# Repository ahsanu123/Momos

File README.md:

# 🐍 Introduction

MoMos - Motor Monitoring System, My Final Undergraduate  Project.  
Its Simple  STM32 connected to Raspberry pi  zero 2w, STM32 was used to  sampling motor vibration and current data, then  Raspberry was used for processing and  displaying to localhost.

contain design board of my final project, and program c/c++ and python.

## 💾 Hardware 

Hardware Actually made from 2 separate PCB, first PCB was used to  breaking  out STM32 Module  Pinout (its not backuped), and second PCB was used to place Raspberry Pi zero 2w.

## 🐉 Schematic

## 🌱 Reference

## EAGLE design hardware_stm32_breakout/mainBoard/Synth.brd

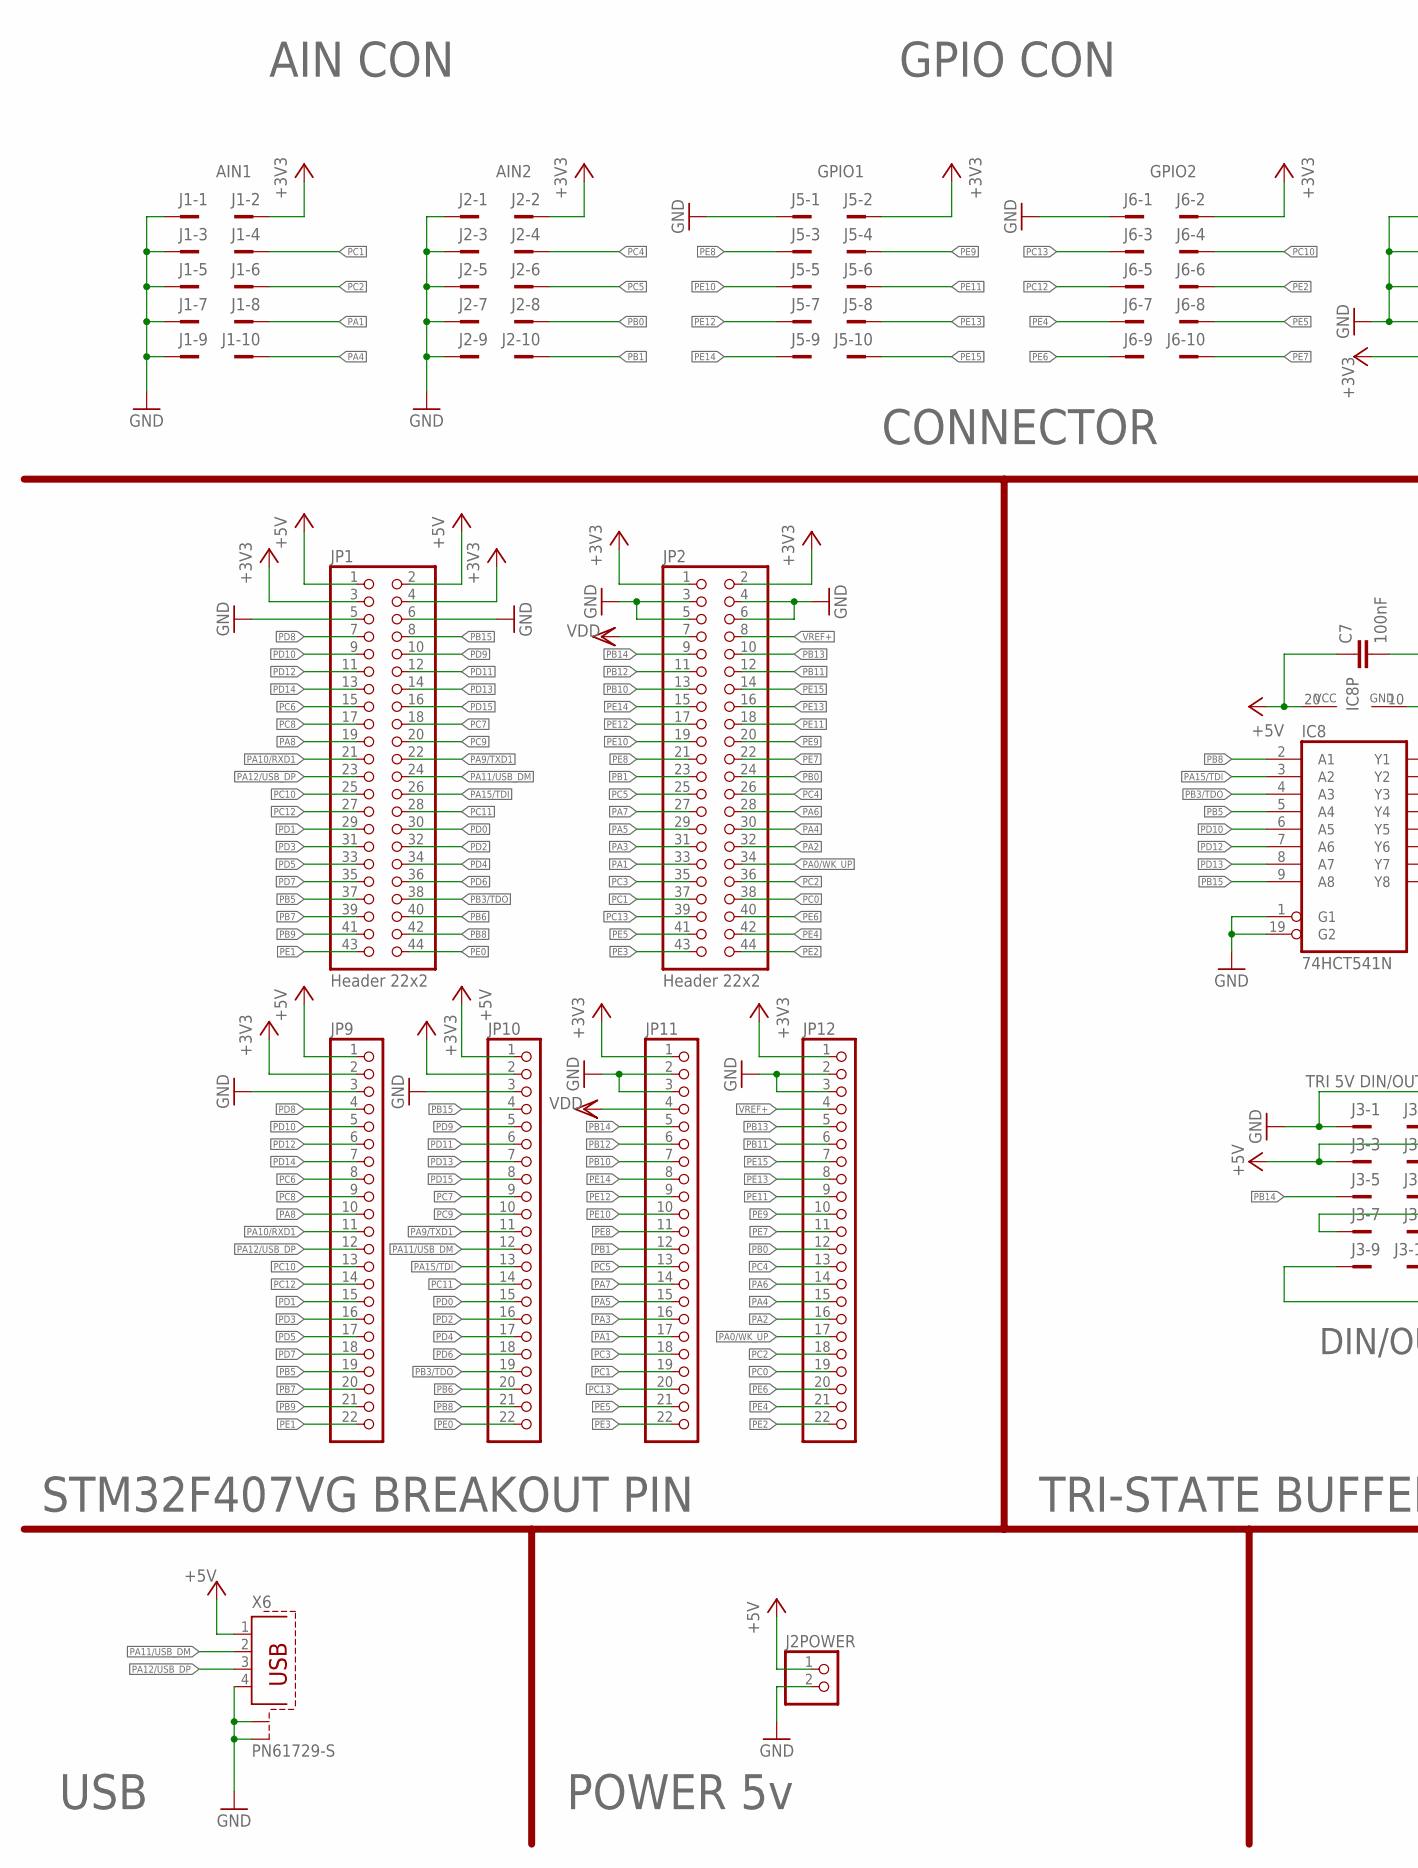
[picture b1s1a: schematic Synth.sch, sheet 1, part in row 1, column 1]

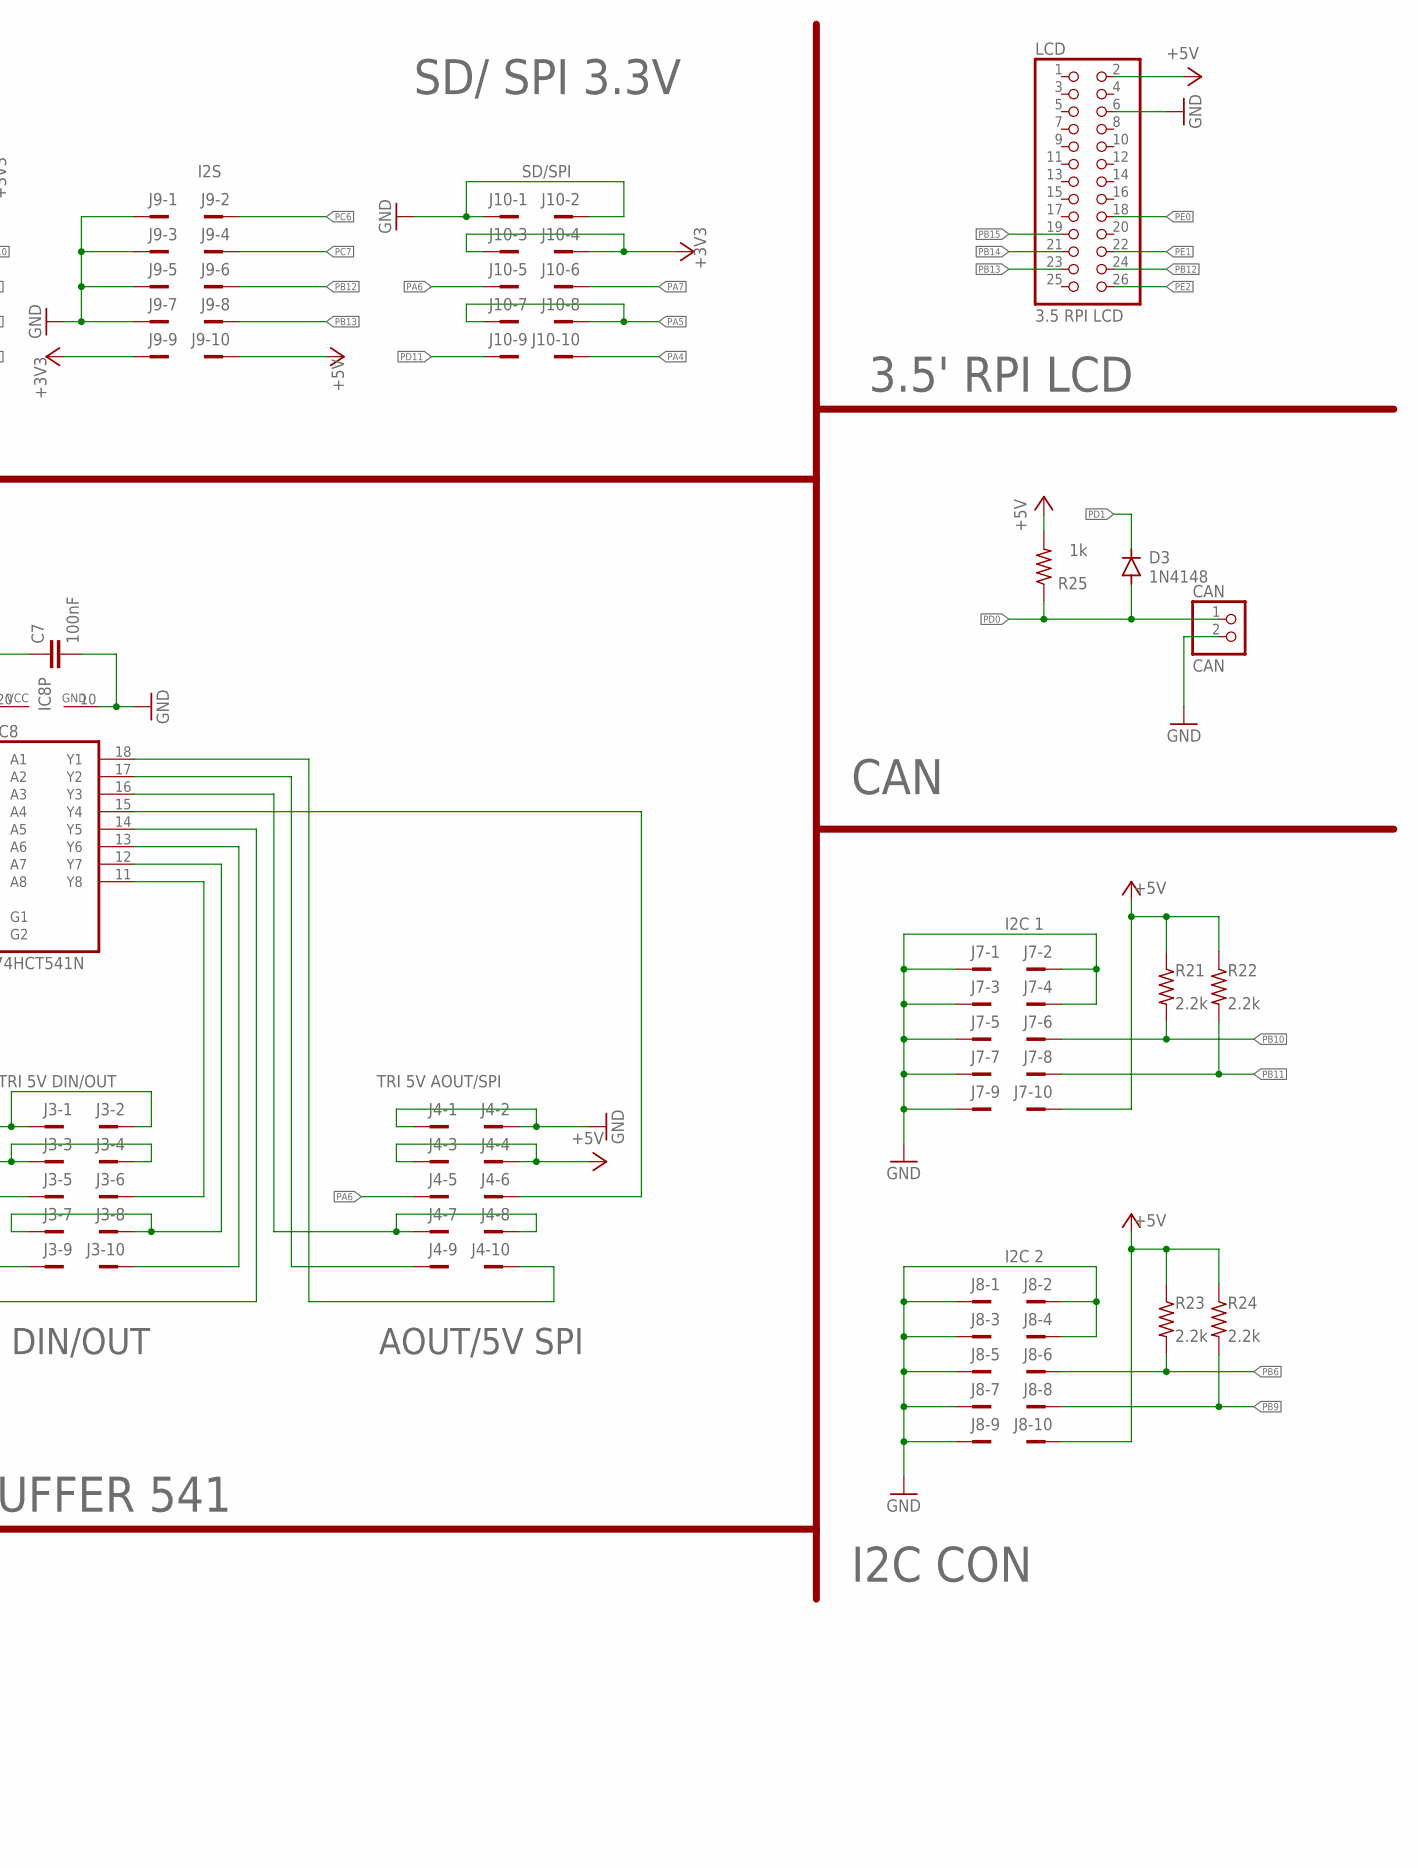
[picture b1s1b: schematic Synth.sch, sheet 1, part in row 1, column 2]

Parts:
C7: 100nF; C025-025X050
CAN: CAN; 1X02
D3: 1N4148; DO35-10
IC8: 74HCT541N; DIL20
J1: AIN1; PAK100/2500-10
J2: AIN2; PAK100/2500-10
J2POWER: PINHD-1X2; 1X02
J3: TRI 5V DIN/OUT; PAK100/2500-10
J4: TRI 5V AOUT/SPI; PAK100/2500-10
J5: GPIO1; PAK100/2500-10
J6: GPIO2; PAK100/2500-10
J7: I2C 1; PAK100/2500-10
J8: I2C 2; PAK100/2500-10
J9: I2S; PAK100/2500-10
J10: SD/SPI; PAK100/2500-10
JP1, JP2: Header 22x2; 2X22
JP9, JP10, JP11, JP12: PINHD-1X22; 1X22
LCD: 3.5 RPI LCD; 2X13
R21, R22, R23, R24: 2.2k; 0207/10
R25: 1k; 0207/10
X6: PN61729-S

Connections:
+3V3: J1.2, J2.2, J5.2, J6.2, J9.9, J10.3, J10.4, JP1.3, JP1.4, JP2.1, JP2.2, JP9.2, JP10.2, JP11.1, JP12.1; also elsewhere on the board
+5V: C7.1, IC8.20 (VCC), J2POWER.1, J3.3, J3.4, J4.3, J4.4, J7.10, J8.10, J9.10, JP1.1, JP1.2, JP9.1, JP10.1, LCD.2, R21.1, R22.1, R23.1, R24.1, R25.2, X6.1; also elsewhere on the board
GND: C7.2, CAN.2, IC8.1 (G1), IC8.10 (GND), IC8.19 (G2), J1.1, J1.3, J1.5, J1.7, J1.9, J2.1, J2.3, J2.5, J2.7, J2.9, J2POWER.2, J3.1, J3.2, J4.1, J4.2, J5.1, J6.1, J7.1, J7.2, J7.3, J7.4, J7.5, J7.7, J7.9, J8.1, J8.2, J8.3, J8.4, J8.5, J8.7, J8.9, J9.1, J9.3, J9.5, J9.7, J10.1, J10.2, JP1.5, JP1.6, JP2.3, JP2.4, JP2.5, JP2.6, JP9.3, JP10.3, JP11.2, JP11.3, JP12.2, JP12.3, LCD.6, X6.4, X6.S1, X6.S2; also elsewhere on the board
unnamed: IC8.15 (Y4), J4.6
unnamed: IC8.12 (Y7), J3.7, J3.8
unnamed: IC8.11 (Y8), J3.6
unnamed: IC8.13 (Y6), J3.10
unnamed: IC8.14 (Y5), J3.9
unnamed: IC8.16 (Y3), J4.7, J4.8
unnamed: IC8.17 (Y2), J4.9
unnamed: IC8.18 (Y1), J4.10
PA0/WK_UP: JP2.34, JP12.17
PA1: J1.8, JP2.33, JP11.17
PA2: JP2.32, JP12.16; also elsewhere on the board
PA3: JP2.31, JP11.16; also elsewhere on the board
PA4: J1.10, J10.10, JP2.30, JP12.15
PA5: J10.7, J10.8, JP2.29, JP11.15
PA6: J4.5, J10.5, JP2.28, JP12.14
PA7: J10.6, JP2.27, JP11.14
PA8: JP1.19, JP9.10; also elsewhere on the board
PA9/TXD1: JP1.22, JP10.11
PA10/RXD1: JP1.21, JP9.11
PA11/USB_DM: JP1.24, JP10.12, X6.2
PA12/USB_DP: JP1.23, JP9.12, X6.3
PA15/TDI: IC8.3 (A2), JP1.26, JP10.13
PB0: J2.8, JP2.24, JP12.12
PB1: J2.10, JP2.23, JP11.12
PB3/TDO: IC8.4 (A3), JP1.38, JP10.19
PB5: IC8.5 (A4), JP1.37, JP9.19
PB6: J8.6, JP1.40, JP10.20, R23.2
PB7: JP1.39, JP9.20
PB8: IC8.2 (A1), JP1.42, JP10.21
PB9: J8.8, JP1.41, JP9.21, R24.2
PB10: J7.6, JP2.13, JP11.7, R21.2
PB11: J7.8, JP2.12, JP12.6, R22.2
PB12: J9.6, JP2.11, JP11.6, LCD.24
PB13: J9.8, JP2.10, JP12.5, LCD.23
PB14: J3.5, JP2.9, JP11.5, LCD.21
PB15: IC8.9 (A8), JP1.8, JP10.4, LCD.19
PC0: JP2.38, JP12.19
PC1: J1.4, JP2.37, JP11.19
PC2: J1.6, JP2.36, JP12.18
PC3: JP2.35, JP11.18
PC4: J2.4, JP2.26, JP12.13
PC5: J2.6, JP2.25, JP11.13
PC6: J9.2, JP1.15, JP9.8
PC7: J9.4, JP1.18, JP10.9
PC8: JP1.17, JP9.9; also elsewhere on the board
PC9: JP1.20, JP10.10
PC10: J6.4, JP1.25, JP9.13
PC11: JP1.28, JP10.14; also elsewhere on the board
PC12: J6.5, JP1.27, JP9.14
PC13: J6.3, JP2.39, JP11.20
PD0: CAN.1, D3.A, JP1.30, JP10.15, R25.1
PD1: D3.C, JP1.29, JP9.15
PD2: JP1.32, JP10.16
PD3: JP1.31, JP9.16; also elsewhere on the board
PD4: JP1.34, JP10.17
PD5: JP1.33, JP9.17
PD6: JP1.36, JP10.18; also elsewhere on the board
PD7: JP1.35, JP9.18
PD8: JP1.7, JP9.4; also elsewhere on the board
PD9: JP1.10, JP10.5; also elsewhere on the board
PD10: IC8.6 (A5), JP1.9, JP9.5
PD11: J10.9, JP1.12, JP10.6
PD12: IC8.7 (A6), JP1.11, JP9.6
PD13: IC8.8 (A7), JP1.14, JP10.7
PD14: JP1.13, JP9.7
PD15: JP1.16, JP10.8
PE0: JP1.44, JP10.22, LCD.18
PE1: JP1.43, JP9.22, LCD.22
PE2: J6.6, JP2.44, JP12.22, LCD.26
PE3: JP2.43, JP11.22
PE4: J6.7, JP2.42, JP12.21
PE5: J6.8, JP2.41, JP11.21
PE6: J6.9, JP2.40, JP12.20
PE7: J6.10, JP2.22, JP12.11
PE8: J5.3, JP2.21, JP11.11
PE9: J5.4, JP2.20, JP12.10
PE10: J5.5, JP2.19, JP11.10
PE11: J5.6, JP2.18, JP12.9
PE12: J5.7, JP2.17, JP11.9
PE13: J5.8, JP2.16, JP12.8
PE14: J5.9, JP2.15, JP11.8
PE15: J5.10, JP2.14, JP12.7
VDD: JP2.7, JP11.4
VREF+: JP2.8, JP12.4

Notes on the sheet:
STM32F407VG BREAKOUT PIN
USB
POWER 5v
AIN CON
GPIO CON
SD/ SPI 3.3V
CONNECTOR
3.5' RPI LCD
CAN
I2C CON
TRI-STATE BUFFER 541
DIN/OUT
AOUT/5V SPI

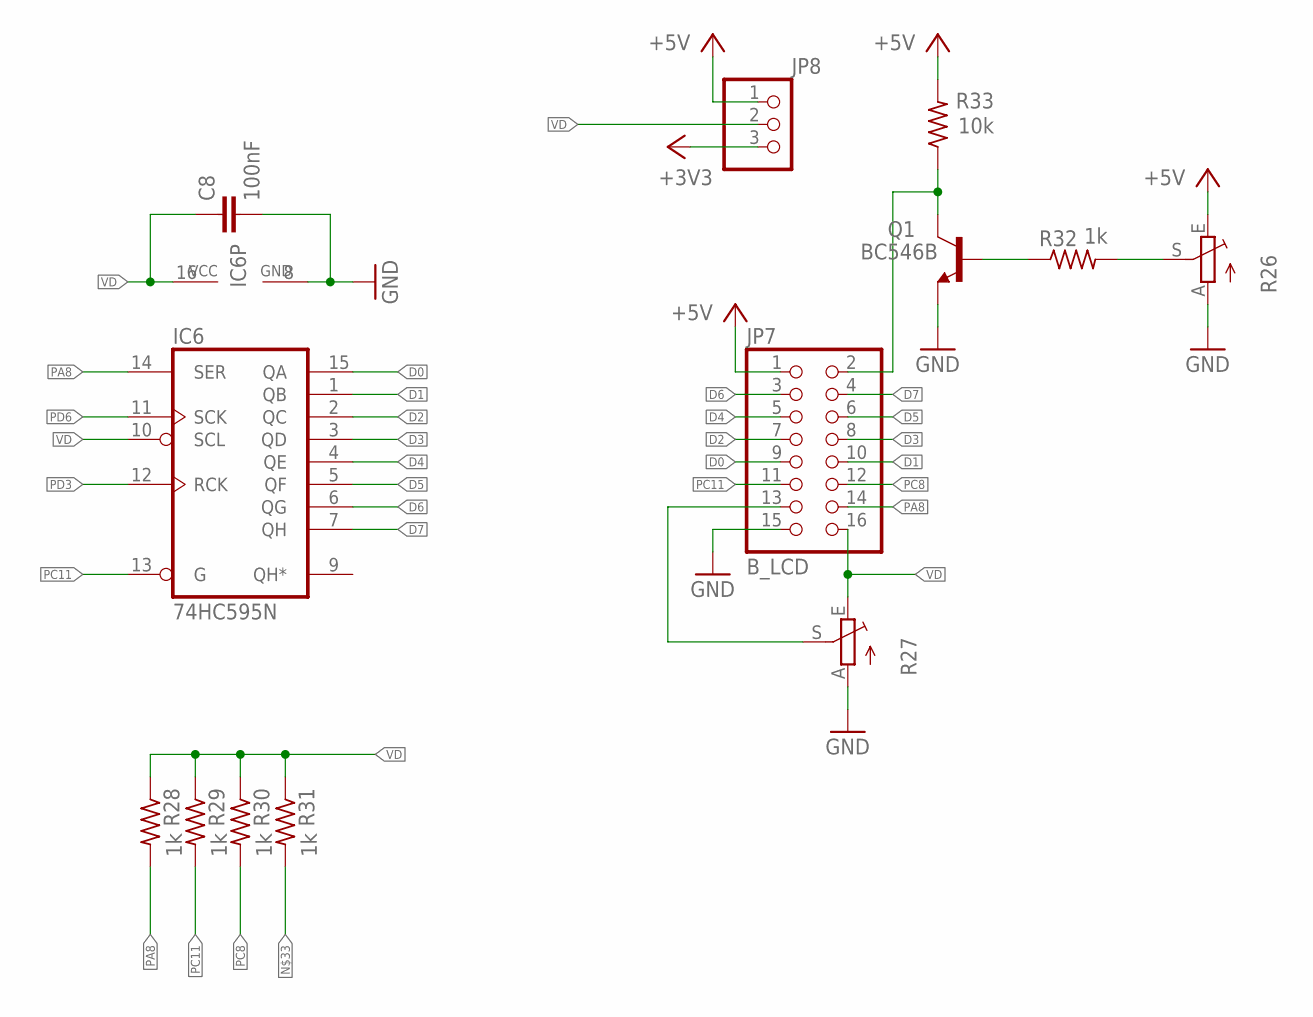
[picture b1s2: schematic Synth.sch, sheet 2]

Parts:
C8: 100nF; C025-025X050
IC6: 74HC595N; DIL16
JP7: B_LCD; 2X08
JP8: PINHD-1X3; 1X03
Q1: BC546B; TO92-EBC
R26, R27: TRIM_EU-CA6V; CA6V
R28, R29, R30, R31, R32: 1k; 0207/10
R33: 10k; 0207/10

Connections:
+3V3: JP8.3; also elsewhere on the board
+5V: JP7.1, JP8.1, R26.E, R33.2; also elsewhere on the board
D0: IC6.15 (QA), JP7.9
D1: IC6.1 (QB), JP7.10
D2: IC6.2 (QC), JP7.7
D3: IC6.3 (QD), JP7.8
D4: IC6.4 (QE), JP7.5
D5: IC6.5 (QF), JP7.6
D6: IC6.6 (QG), JP7.3
D7: IC6.7 (QH), JP7.4
GND: C8.2, IC6.8 (GND), JP7.15, Q1.E, R26.A, R27.A; also elsewhere on the board
unnamed: JP7.13, R27.S
unnamed: JP7.2, Q1.C, R33.1
unnamed: Q1.B, R32.1
unnamed: R26.S, R32.2
PA8: IC6.14 (SER), JP7.14, R28.2; also elsewhere on the board
PC8: JP7.12, R30.2; also elsewhere on the board
PC11: IC6.13 (G), JP7.11, R29.2; also elsewhere on the board
PD3: IC6.12 (RCK); also elsewhere on the board
PD6: IC6.11 (SCK); also elsewhere on the board
VD: C8.1, IC6.10 (SCL), IC6.16 (VCC), JP7.16, JP8.2, R27.E, R28.1, R29.1, R30.1, R31.1

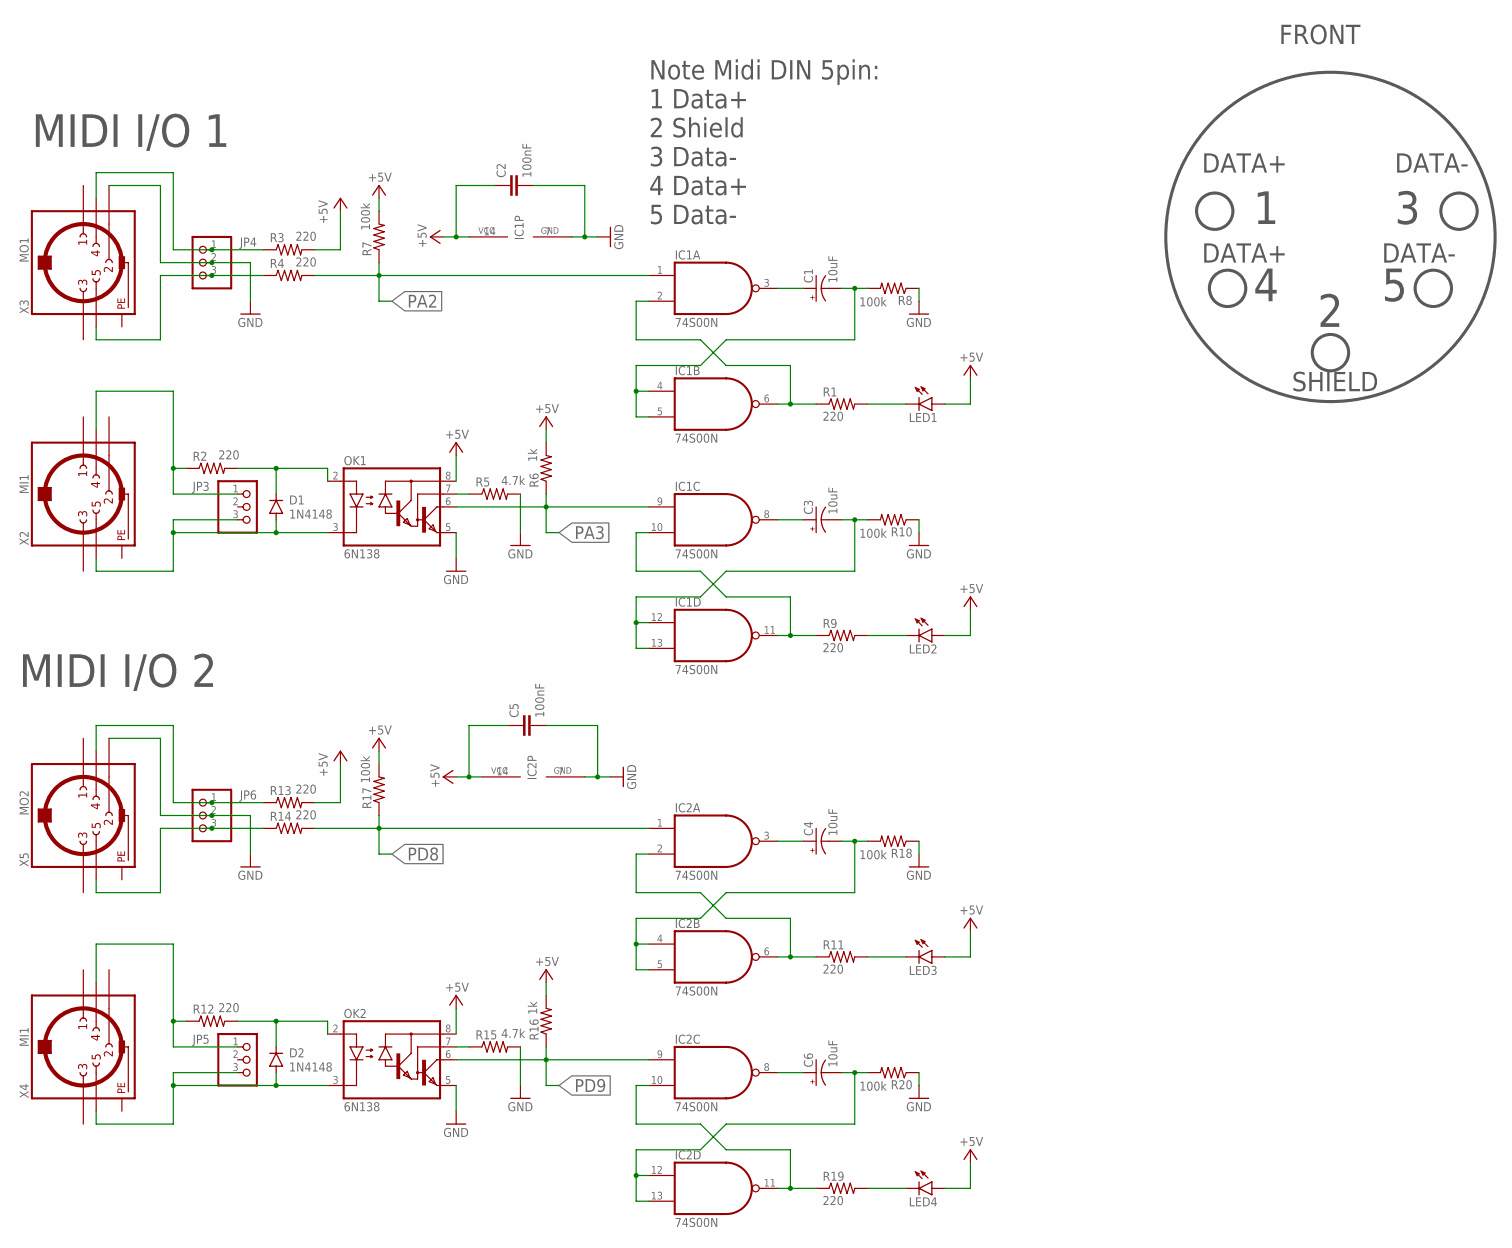
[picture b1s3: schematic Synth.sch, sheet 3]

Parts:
C1, C3, C4, C6: 10uF; E3,5-8
C2, C5: 100nF; C025-025X050
D1, D2: 1N4148; DO35-10
IC1, IC2: 74S00N; DIL14
JP3, JP4, JP5, JP6: PINHD-1X3; 1X03
LED1, LED2, LED3, LED4: LED3MM
OK1, OK2: 6N138; DIL08
R1, R2, R3, R4, R9, R11, R12, R13, R14, R19: 220; 0207/10
R5, R15: 4.7k; 0207/10
R6, R16: 1k; 0207/10
R7, R8, R10, R17, R18, R20: 100k; 0207/10
X2, X4: MI1; MAB5SH
X3: MO1; MAB5SH
X5: MO2; MAB5SH

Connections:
+5V: C2.1, C5.1, IC1.14 (VCC), IC2.14 (VCC), LED1.A, LED2.A, LED3.A, LED4.A, OK1.8 (VCC), OK2.8 (VCC), R3.2, R6.2, R7.2, R13.2, R16.2, R17.2; also elsewhere on the board
GND: C2.2, C5.2, IC1.7 (GND), IC2.7 (GND), JP4.2, JP6.2, OK1.5 (GND), OK2.5 (GND), R5.2, R8.1, R10.1, R15.2, R18.1, R20.1, X3.2, X5.2; also elsewhere on the board
unnamed: D1.C, OK1.2 (A), R2.2
unnamed: D1.A, JP3.3, OK1.3 (C), X2.5
unnamed: JP3.1, R2.1, X2.4
unnamed: D2.C, OK2.2 (A), R12.2
unnamed: OK1.7 (VB), R5.1
unnamed: JP4.3, R4.1, X3.5
unnamed: D2.A, JP5.3, OK2.3 (C), X4.5
unnamed: JP4.1, R3.1, X3.4
unnamed: IC1.2 (I1), IC1.6 (O), R1.1
unnamed: C1.-, IC1.4 (I0), IC1.5 (I1), R8.2
unnamed: C1.+, IC1.3 (O)
unnamed: LED1.K (C), R1.2
unnamed: IC1.10 (I1), IC1.11 (O), R9.1
unnamed: C3.-, IC1.12 (I0), IC1.13 (I1), R10.2
unnamed: C3.+, IC1.8 (O)
unnamed: LED2.K (C), R9.2
unnamed: JP5.1, R12.1, X4.4
unnamed: JP6.3, R14.1, X5.5
unnamed: JP6.1, R13.1, X5.4
unnamed: OK2.7 (VB), R15.1
unnamed: IC2.2 (I1), IC2.6 (O), R11.1
unnamed: C4.-, IC2.4 (I0), IC2.5 (I1), R18.2
unnamed: C4.+, IC2.3 (O)
unnamed: LED3.K (C), R11.2
unnamed: IC2.10 (I1), IC2.11 (O), R19.1
unnamed: C6.-, IC2.12 (I0), IC2.13 (I1), R20.2
unnamed: C6.+, IC2.8 (O)
unnamed: LED4.K (C), R19.2
PA2: IC1.1 (I0), R4.2, R7.1; also elsewhere on the board
PA3: IC1.9 (I0), OK1.6 (VO), R6.1; also elsewhere on the board
PD8: IC2.1 (I0), R14.2, R17.1; also elsewhere on the board
PD9: IC2.9 (I0), OK2.6 (VO), R16.1; also elsewhere on the board
PE: X2.PE, X2.PE@ (PE), X3.PE, X3.PE@ (PE), X4.PE, X4.PE@ (PE), X5.PE, X5.PE@ (PE)

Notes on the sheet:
Note Midi DIN 5pin: 1 Data+ 2 Shield 3 Data- 4 Data+ 5 Data-
MIDI I/O 1
MIDI I/O 2
FRONT
DATA+
DATA-
SHIELD

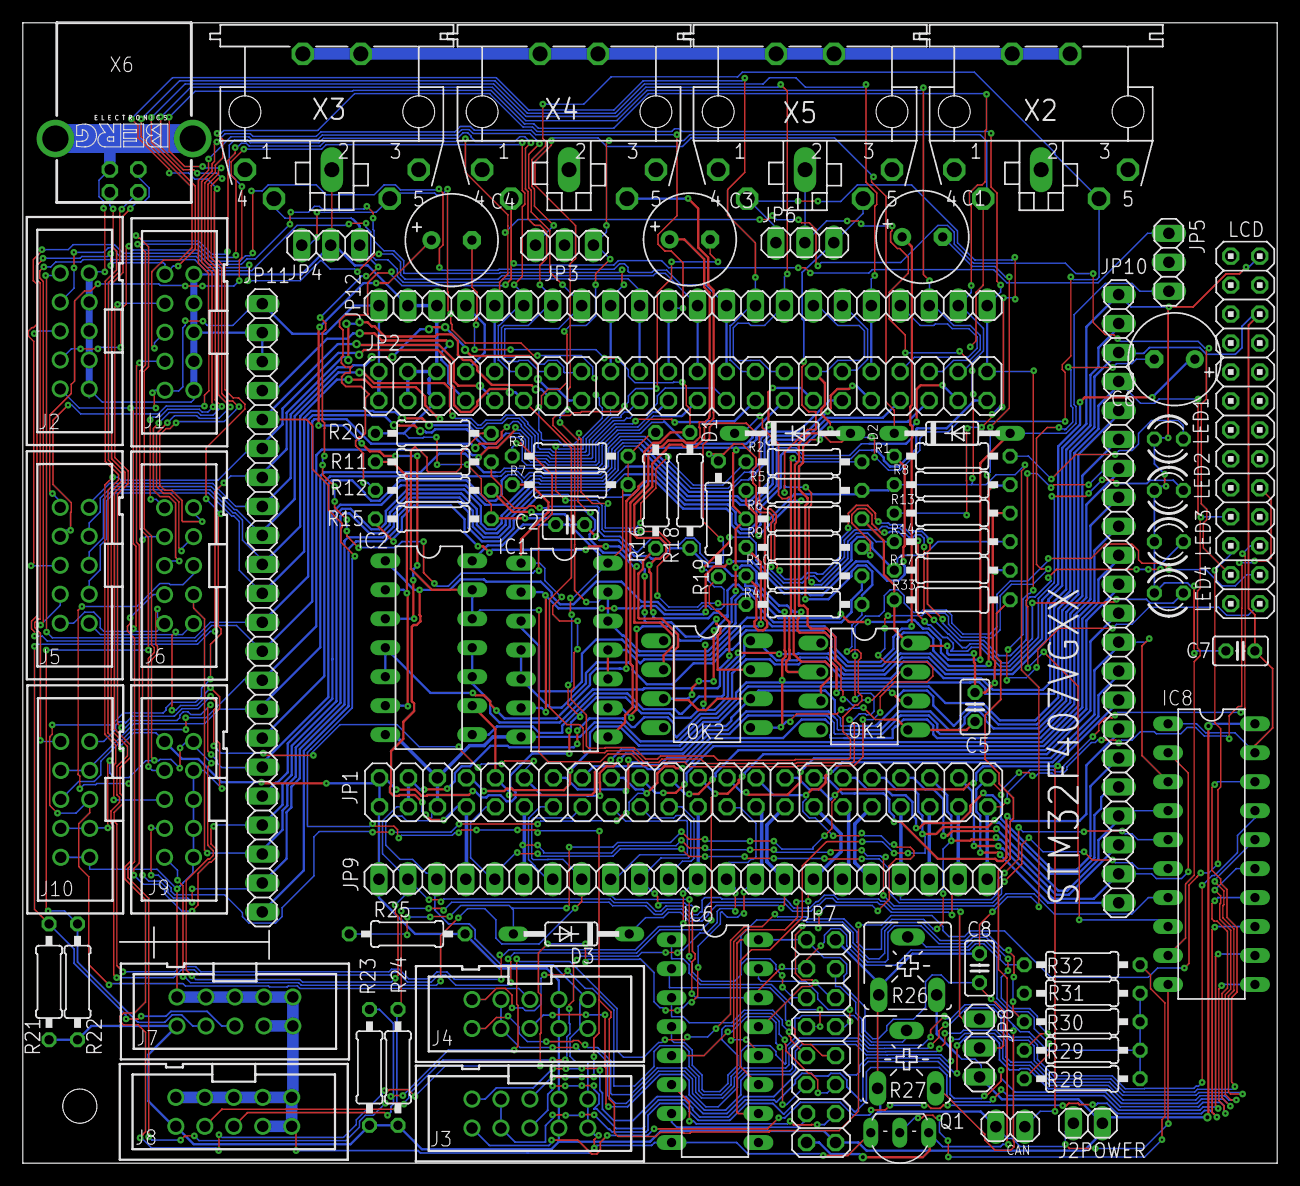
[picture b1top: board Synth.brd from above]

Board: 2 copper layers, 110.0 x 100.0 mm, 85 parts (0 on the bottom side), 129 nets.

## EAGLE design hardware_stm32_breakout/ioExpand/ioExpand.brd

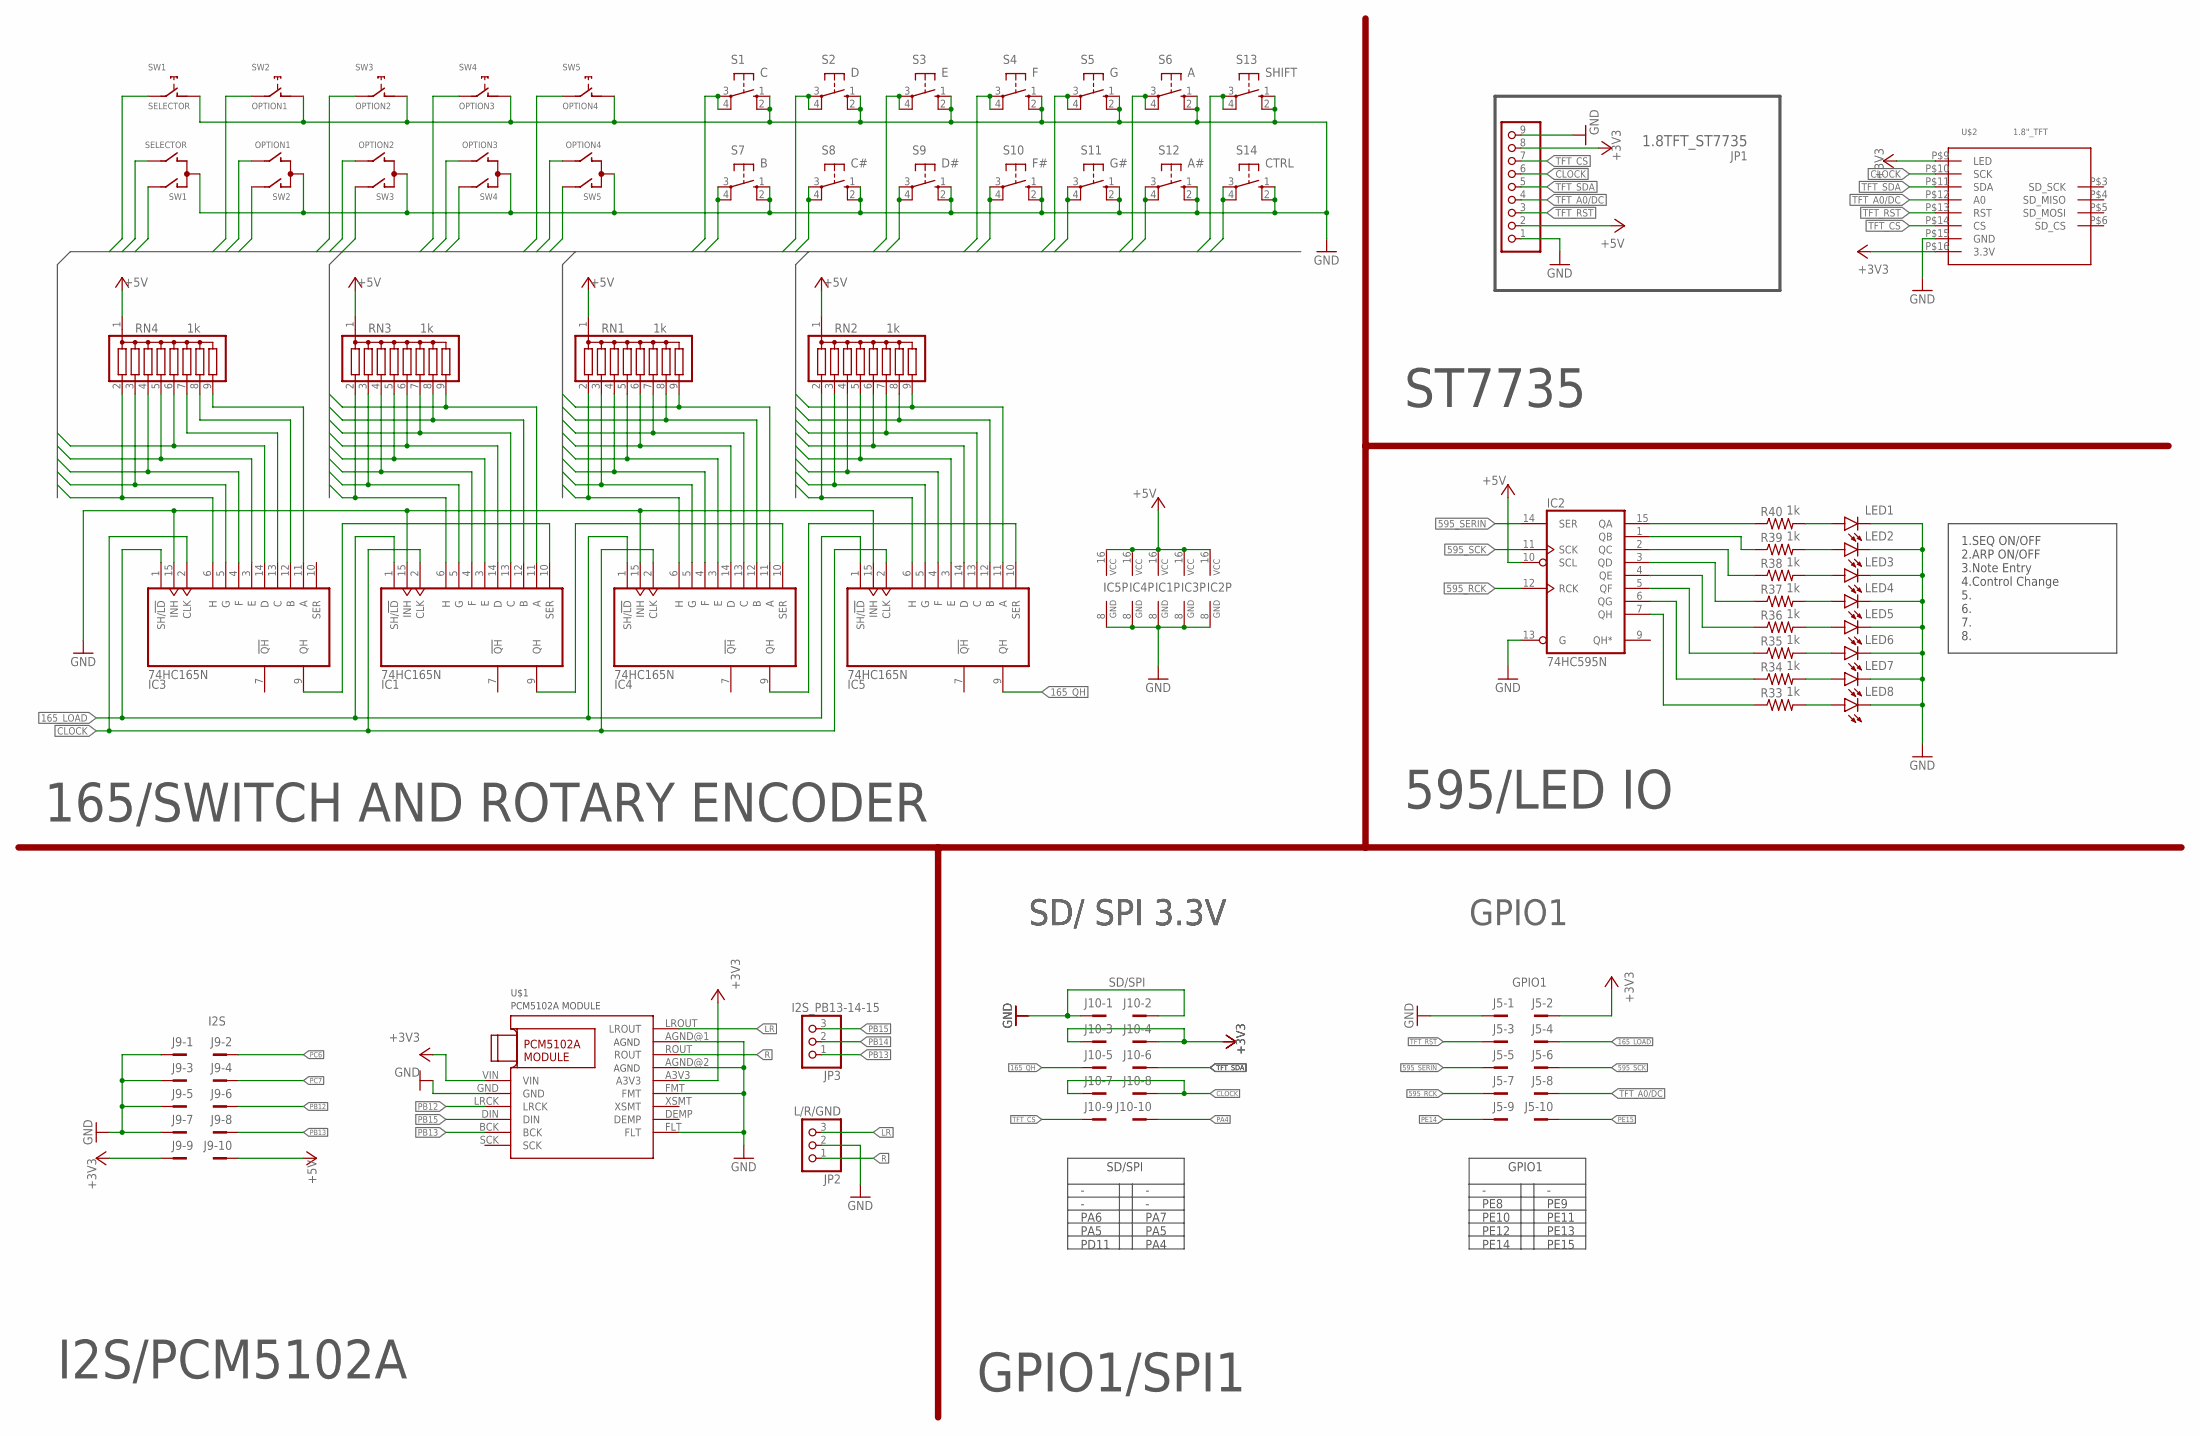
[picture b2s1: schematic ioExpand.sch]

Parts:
IC1, IC3, IC4, IC5: 74HC165N; DIL16
IC2: 74HC595N; DIL16
J5: GPIO1; PAK100/2500-10
J9: I2S; PAK100/2500-10
J10: SD/SPI; PAK100/2500-10
JP1: 1.8TFT_ST7735; 1X09
JP2: L/R/GND; 1X03
JP3: I2S_PB13-14-15; 1X03
LED1, LED2, LED3, LED4, LED5, LED6, LED7, LED8: LED3MM
R33, R34, R35, R36, R37, R38, R39, R40: 1k; M1206
RN1, RN2, RN3, RN4: 1k; SIL9
S1: C; B3F-40XX
S2: D; B3F-40XX
S3: E; B3F-40XX
S4: F; B3F-40XX
S5: G; B3F-40XX
S6: A; B3F-40XX
S7: B; B3F-40XX
S8: C#; B3F-40XX
S9: D#; B3F-40XX
S10: F#; B3F-40XX
S11: G#; B3F-40XX
S12: A#; B3F-40XX
S13: SHIFT; B3F-40XX
S14: CTRL; B3F-40XX
SW1: SELECTOR; ALPS_EC12E_SW
SW2: OPTION1; ALPS_EC12E_SW
SW3: OPTION2; ALPS_EC12E_SW
SW4: OPTION3; ALPS_EC12E_SW
SW5: OPTION4; ALPS_EC12E_SW
U$1: PCM5102A_MODULE
U$2: 1.8"_TFT

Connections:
165_LOAD: IC1.1 (SH/!LD), IC3.1 (SH/!LD), IC4.1 (SH/!LD), IC5.1 (SH/!LD), J5.4
165_QH: IC5.9 (QH), J10.5
595_RCK: IC2.12 (RCK), J5.7
595_SCK: IC2.11 (SCK), J5.6
595_SERIN: IC2.14 (SER), J5.5
$123: IC3.13 (C), RN4.7
+3V3: J5.2, J9.9, J10.3, J10.4, JP1.8, U$1.A3V3, U$1.VIN, U$2.P$9 (LED), U$2.P$16 (3.3V)
+5V: IC1.16 (VCC), IC2.10 (SCL), IC2.16 (VCC), IC3.16 (VCC), IC4.16 (VCC), IC5.16 (VCC), J9.10, JP1.2, RN1.1, RN2.1, RN3.1, RN4.1
CLOCK: IC1.2 (CLK), IC3.2 (CLK), IC4.2 (CLK), IC5.2 (CLK), J10.7, J10.8, JP1.6, U$2.P$10 (SCK)
CTRL: IC3.3 (E), RN4.5, S14.3, S14.4 (P1)
GND: IC1.8 (GND), IC1.15 (INH), IC2.8 (GND), IC2.13 (G), IC3.8 (GND), IC3.15 (INH), IC4.8 (GND), IC4.15 (INH), IC5.8 (GND), IC5.15 (INH), J5.1, J9.1, J9.3, J9.5, J9.7, J10.1, J10.2, JP1.1, JP1.9, JP2.2, LED1.K (C), LED2.K (C), LED3.K (C), LED4.K (C), LED5.K (C), LED6.K (C), LED7.K (C), LED8.K (C), S1.1 (S), S1.2 (S1), S2.1 (S), S2.2 (S1), S3.1 (S), S3.2 (S1), S4.1 (S), S4.2 (S1), S5.1 (S), S5.2 (S1), S6.1 (S), S6.2 (S1), S7.1 (S), S7.2 (S1), S8.1 (S), S8.2 (S1), S9.1 (S), S9.2 (S1), S10.1 (S), S10.2 (S1), S11.1 (S), S11.2 (S1), S12.1 (S), S12.2 (S1), S13.1 (S), S13.2 (S1), S14.1 (S), S14.2 (S1), SW1.C, SW1.D (1), SW2.C, SW2.D (1), SW3.C, SW3.D (1), SW4.C, SW4.D (1), SW5.C, SW5.D (1), U$1.AGND@1 (AGND), U$1.AGND@2 (AGND), U$1.FLT, U$1.FMT, U$1.GND, U$2.P$15 (GND)
KEY1: IC1.11 (A), RN3.9, S1.3, S1.4 (P1)
KEY2: IC1.13 (C), RN3.7, S2.3, S2.4 (P1)
KEY3: IC1.3 (E), RN3.5, S3.3, S3.4 (P1)
KEY4: IC1.4 (F), RN3.4, S4.3, S4.4 (P1)
KEY5: IC4.11 (A), RN1.9, S5.3, S5.4 (P1)
KEY6: IC4.12 (B), RN1.8, S6.3, S6.4 (P1)
KEY7: IC4.14 (D), RN1.6, S7.3, S7.4 (P1)
KEY8: IC1.12 (B), RN3.8, S8.3, S8.4 (P1)
KEY9: IC1.14 (D), RN3.6, S9.3, S9.4 (P1)
KEY10: IC1.5 (G), RN3.3, S10.3, S10.4 (P1)
KEY11: IC1.6 (H), RN3.2, S11.3, S11.4 (P1)
KEY12: IC4.13 (C), RN1.7, S12.3, S12.4 (P1)
LR: JP2.3, U$1.LROUT
unnamed: IC2.15 (QA), R40.1
unnamed: IC2.1 (QB), R39.1
unnamed: IC2.2 (QC), R38.1
unnamed: IC2.3 (QD), R37.1
unnamed: IC2.4 (QE), R36.1
unnamed: IC2.5 (QF), R35.1
unnamed: IC2.6 (QG), R34.1
unnamed: IC2.7 (QH), R33.1
unnamed: LED1.A, R40.2
unnamed: LED8.A, R33.2
unnamed: LED7.A, R34.2
unnamed: LED6.A, R35.2
unnamed: LED5.A, R36.2
unnamed: LED4.A, R37.2
unnamed: LED3.A, R38.2
unnamed: LED2.A, R39.2
unnamed: IC1.10 (SER), IC3.9 (QH)
unnamed: IC1.9 (QH), IC4.10 (SER)
unnamed: IC4.9 (QH), IC5.10 (SER)
unnamed: IC3.11 (A), RN4.9
unnamed: IC3.12 (B), RN4.8
PA4: J10.10
PB12: J9.6, U$1.LRCK
PB13: J9.8, JP3.1, U$1.BCK
PB14: JP3.2
PB15: JP3.3, U$1.DIN
PC6: J9.2
PC7: J9.4
PE14: J5.9
PE15: J5.10
R: JP2.1, U$1.ROUT
ROTSW1: IC3.6 (H), RN4.2, SW1.E (2)
ROTSW2: IC5.6 (H), RN2.2, SW2.E (2)
ROTSW3: IC5.3 (E), RN2.5, SW3.E (2)
ROTSW4: IC5.12 (B), RN2.8, SW4.E (2)
ROTSW5: IC4.5 (G), RN1.3, SW5.E (2)
ROTSW_AB1: IC3.5 (G), RN4.3, SW1.B
ROTSW_AB2: IC3.4 (F), RN4.4, SW1.A
ROTSW_AB3: IC5.5 (G), RN2.3, SW2.B
ROTSW_AB4: IC5.4 (F), RN2.4, SW2.A
ROTSW_AB5: IC5.14 (D), RN2.6, SW3.B
ROTSW_AB6: IC5.13 (C), RN2.7, SW3.A
ROTSW_AB7: IC5.11 (A), RN2.9, SW4.B
ROTSW_AB8: IC4.6 (H), RN1.2, SW4.A
ROTSW_AB9: IC4.4 (F), RN1.4, SW5.B
ROTSW_AB10: IC4.3 (E), RN1.5, SW5.A
SHIFT: IC3.14 (D), RN4.6, S13.3, S13.4 (P1)
TFT_A0/DC: J5.8, JP1.4, U$2.P$12 (A0)
TFT_CS: J10.9, JP1.7, U$2.P$14 (CS)
TFT_RST: J5.3, JP1.3, U$2.P$13 (RST)
TFT_SDA: J10.6, JP1.5, U$2.P$11 (SDA)

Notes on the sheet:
SD/ SPI 3.3V
- - PA6 PA5 PD11
- - PA7 PA5 PA4
SD/SPI
- PE8 PE10 PE12 PE14
- PE9 PE11 PE13 PE15
GPIO1
1.SEQ ON/OFF 2.ARP ON/OFF 3.Note Entry 4.Control Change 5. 6. 7. 8.
ST7735
595/LED IO
GPIO1/SPI1
I2S/PCM5102A
165/SWITCH AND ROTARY ENCODER

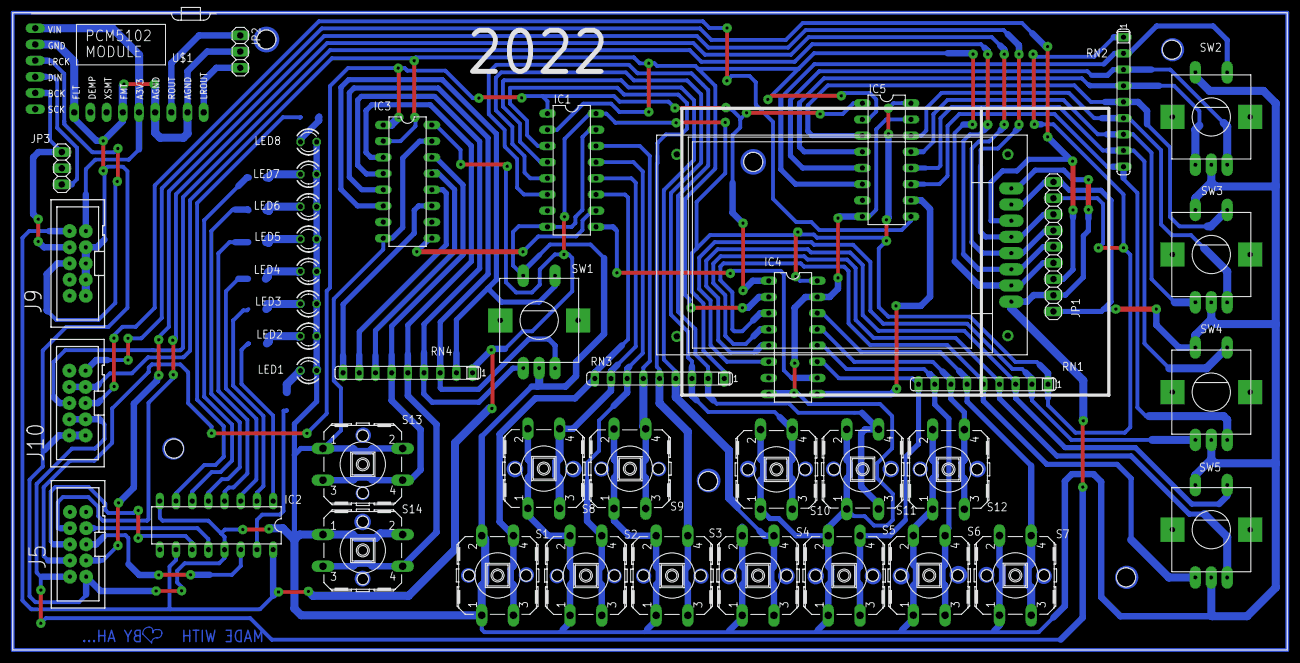
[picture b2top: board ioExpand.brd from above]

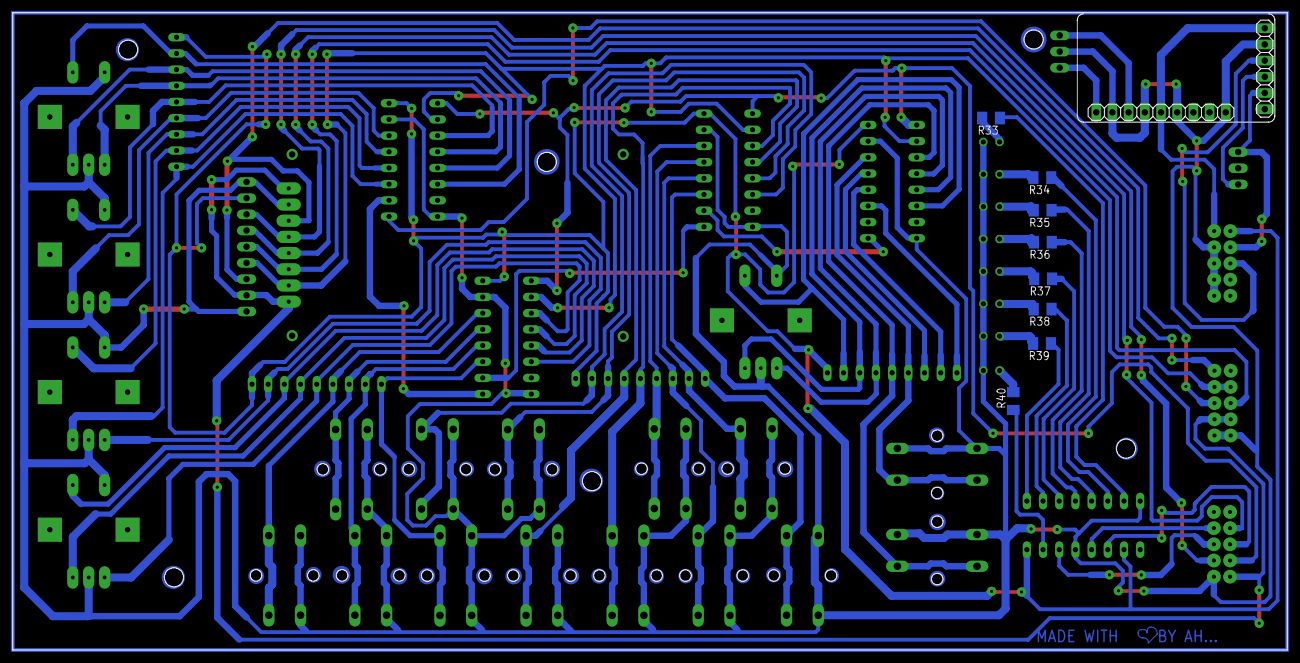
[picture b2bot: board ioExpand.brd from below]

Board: 2 copper layers, 200.0 x 100.0 mm, 52 parts (8 on the bottom side), 69 nets.

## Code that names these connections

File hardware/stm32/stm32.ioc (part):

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Mcu.Name=STM32F407V(E-G)Tx
Mcu.Package=LQFP100
Mcu.UserName=STM32F407VGTx
PA1.Signal=ADCx_IN1
PA11.Mode=Device_Only
PA11.Signal=USB_OTG_FS_DM
PA12.Mode=Device_Only
PA12.Signal=USB_OTG_FS_DP
PA4.Signal=ADCx_IN4
PA5.Mode=Full_Duplex_Master
PA5.Signal=SPI1_SCK
PA6.Mode=Full_Duplex_Master
PA6.Signal=SPI1_MISO
PA7.Mode=Full_Duplex_Master
PA7.Signal=SPI1_MOSI
PB10.Mode=Asynchronous
PB10.Signal=USART3_TX
PB11.Mode=Asynchronous
PB11.Signal=USART3_RX
PB6.Mode=I2C
PB6.Signal=I2C1_SCL
PB9.Mode=I2C
PB9.Signal=I2C1_SDA
PC1.Signal=ADCx_IN11
PC10.Mode=SD_4_bits_Wide_bus
PC10.Signal=SDIO_D2
PC11.Mode=SD_4_bits_Wide_bus
PC11.Signal=SDIO_D3
PC12.Mode=SD_4_bits_Wide_bus
PC12.Signal=SDIO_CK
PC2.Signal=ADCx_IN12
PC8.Mode=SD_4_bits_Wide_bus
PC8.Signal=SDIO_D0
PC9.Mode=SD_4_bits_Wide_bus
PC9.Signal=SDIO_D1
PD2.Mode=SD_4_bits_Wide_bus
PD2.Signal=SDIO_CMD
PH0-OSC_IN.Mode=HSE-External-Oscillator
PH0-OSC_IN.Signal=RCC_OSC_IN
PH1-OSC_OUT.Mode=HSE-External-Oscillator
PH1-OSC_OUT.Signal=RCC_OSC_OUT
RCC.HSE_VALUE=8000000
RCC.SYSCLKFreq_VALUE=168000000
RCC.SYSCLKSource=RCC_SYSCLKSOURCE_PLLCLK
board=custom

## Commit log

2023-04-06 modified: 2023_04_06__090647.csv
2023-04-06 Changes to be committed: new file: README.md
2023-04-21 working with plotly
2023-05-08 backup 8 mei 2023
2023-05-14 backup before use matplotlib
2023-06-10 add .gitignore file
2023-06-10 after struggling with ssh
2023-06-10 change gitignore
2023-06-10 change again gitignore
2023-06-10 remove pycache
2023-06-10 add hardware folder
2023-06-10 edit readme
2025-02-04 [02-04-2025] re-structuring momos project
2025-02-04 [02-04-1503] adding stm32 cpp folder to repo
2025-02-04 [02-04-1509] adding stm32 breakout board schematic
